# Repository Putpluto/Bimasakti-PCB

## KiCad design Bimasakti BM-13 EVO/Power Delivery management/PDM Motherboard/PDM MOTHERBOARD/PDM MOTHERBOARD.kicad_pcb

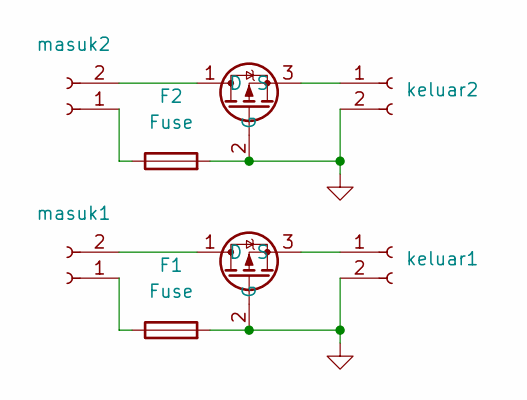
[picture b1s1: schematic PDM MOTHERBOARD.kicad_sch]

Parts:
F1, F2: Fuse; Fuseholder_Clip-5x20mm_Bel_FC-203-22_Lateral_P17.80x5.00mm_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
U1, U2: SOIC-8 (AOD)
keluar1, keluar2: JST_EH_B2B-EH-A_1x02_P2.50mm_Vertical
masuk1, masuk2: JST_EH_B2B-EH-A_1x02_P2.50mm_Vertical

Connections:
GND: F1.2, F2.2, U1.2 (G), U2.2 (G), keluar1.2, keluar2.2
unnamed: U1.1 (D), masuk1.2
unnamed: U1.3 (S), keluar1.1
unnamed: U2.1 (D), masuk2.2
unnamed: U2.3 (S), keluar2.1
unnamed: F1.1, masuk1.1
unnamed: F2.1, masuk2.1

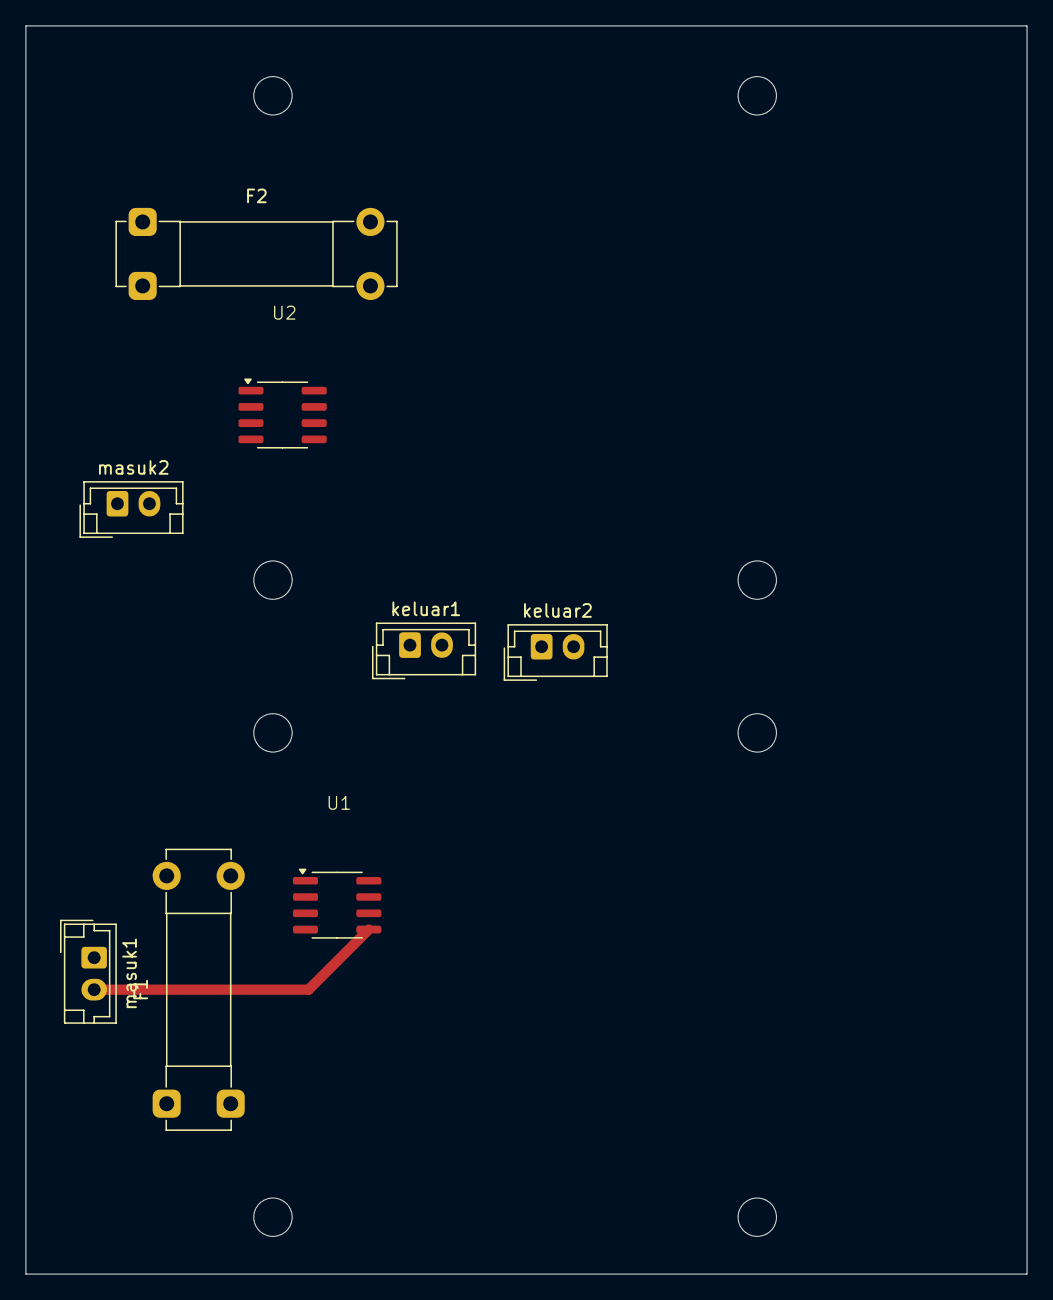
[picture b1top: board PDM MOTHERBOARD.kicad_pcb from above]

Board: 2 copper layers, 78.2 x 97.5 mm, 8 parts (0 on the bottom side), 7 nets.

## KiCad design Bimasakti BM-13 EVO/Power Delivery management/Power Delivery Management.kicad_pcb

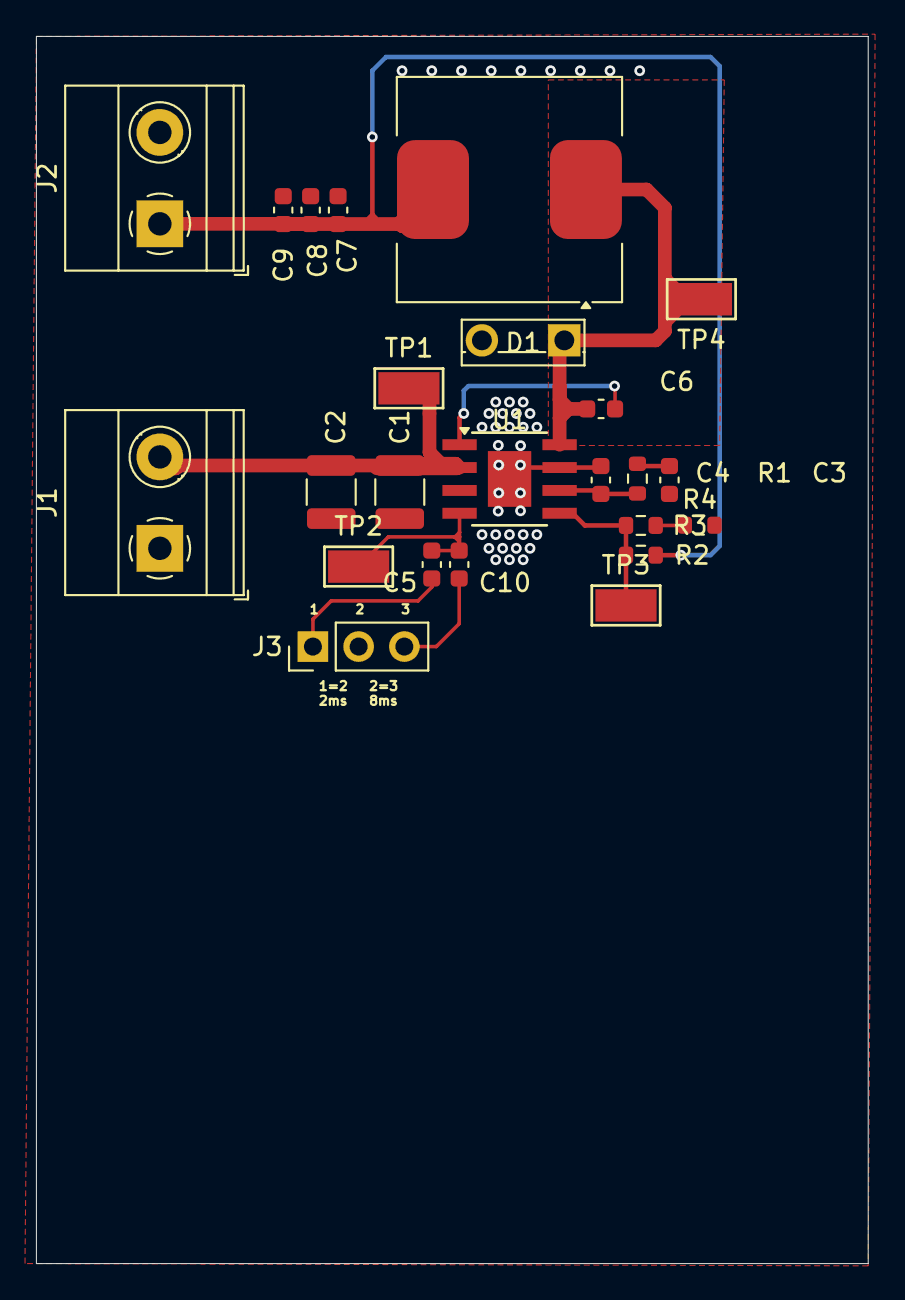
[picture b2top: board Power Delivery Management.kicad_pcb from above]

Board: 4 copper layers, 46.2 x 68.2 mm, 24 parts (0 on the bottom side), 12 nets.

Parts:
C1, C2: 22uF; C_1210_3225Metric
C3: 1nF; C_0603_1608Metric
C4: 10pF; C_0603_1608Metric
C5: 5nF; C_0603_1608Metric
C6: 100nF; C_0603_1608Metric
C7, C8, C9: 47uF; C_0603_1608Metric
C10: 20nF; C_0603_1608Metric
D1: 950mV 10A; TO-251-2_Vertical
J1: 12V Accu; TerminalBlock_Phoenix_MKDS-1,5-2-5.08_1x02_P5.08mm_Horizont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
J2: 5V Out; TerminalBlock_Phoenix_MKDS-1,5-2-5.08_1x02_P5.08mm_Horizont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
J3: Slow Start; PinHeader_1x03_P2.54mm_Vertical
L1: 12uH; L_Coilcraft_MSS1278T-XXX
R1: 50k; R_0603_1608Metric
R2: 10k; R_0603_1608Metric
R3: 1.5k; R_0603_1608Metric
R4: 390; R_0603_1608Metric
TP1, TP2, TP3, TP4: TestPoint; TestPoint_Keystone_5015_Micro-Minature
U1: TI_SO-PowerPAD-8

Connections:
+12V: C1.1, C2.1, J1.2, TP1.1, U1.2 (Vin)
/+5V: C7.1, C8.1, C9.1, J2.1, L1.2, R2.1
BOOT: C6.1, U1.1 (BOOT)
COMP: C4.1, R1.1, U1.6 (COMP)
GND: C1.2, C2.2, C3.2, C4.2, C7.2, C8.2, C9.2, D1.2 (A), J1.1, J2.2, J3.2, R4.2, U1.7 (GND), U1.9 (Power_PAD)
unnamed: C3.1, R1.2
unnamed: R3.1, R4.1
unnamed: C5.2, C10.2, TP2.1, U1.4 (SS)
PH: C6.2, D1.1 (K), L1.1, TP4.1, U1.8 (PH)
SS1: C5.1, J3.1
SS2: C10.1, J3.3
VSENSE: R2.2, R3.2, TP3.1, U1.5 (VSENSE)

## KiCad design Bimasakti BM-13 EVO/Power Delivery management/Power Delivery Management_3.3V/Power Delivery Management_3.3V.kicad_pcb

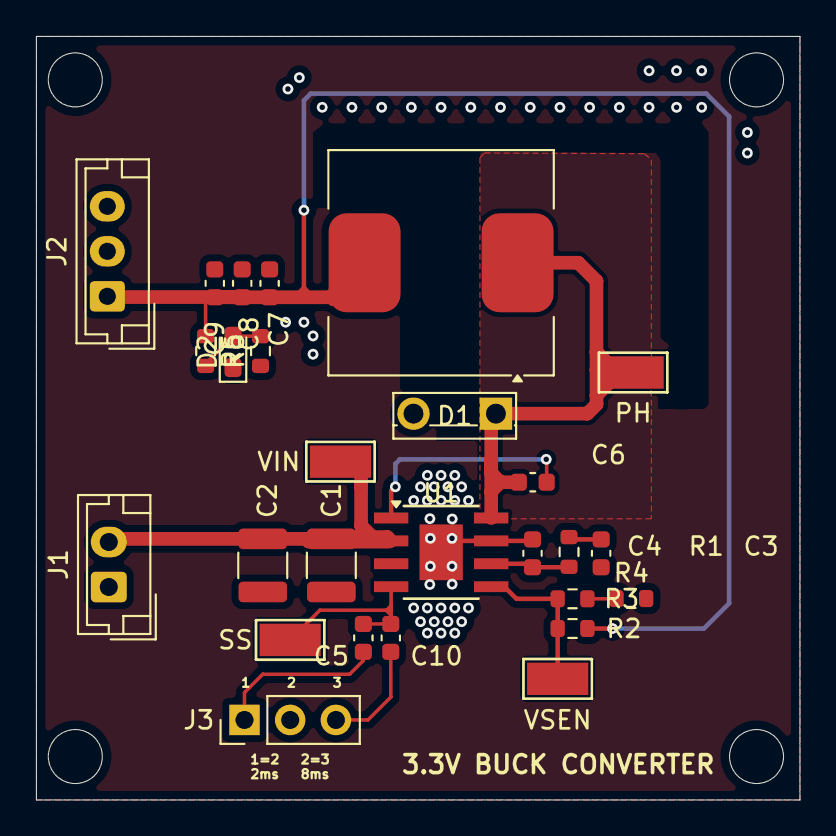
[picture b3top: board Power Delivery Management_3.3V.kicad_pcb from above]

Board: 2 copper layers, 42.4 x 42.4 mm, 27 parts (0 on the bottom side), 2 nets.

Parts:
C1, C2: 22uF; C_1210_3225Metric
C3: 1nF; C_0603_1608Metric
C4: 10pF; C_0603_1608Metric
C5: 5nF; C_0603_1608Metric
C6: 100nF; C_0603_1608Metric
C7, C8, C9: 47uF; C_0603_1608Metric
C10: 20nF; C_0603_1608Metric
D1: 950mV 10A; TO-251-2_Vertical
D2: LED; LED_0603_1608Metric_Pad1.05x0.95mm_HandSolder
J1: +12V In; JST_EH_B2B-EH-A_1x02_P2.50mm_Vertical
J2: Conn_01x03_Socket; JST_EH_B3B-EH-A_1x03_P2.50mm_Vertical
J3: Slow Start; PinHeader_1x03_P2.54mm_Vertical
L1: 12uH; L_Coilcraft_MSS1278T-XXX
PH: TestPoint; TestPoint_Keystone_5015_Micro-Minature
R1: 50k; R_0603_1608Metric
R2: 10k; R_0603_1608Metric
R3, R6: 1.5k; R_0603_1608Metric
R4: 390; R_0603_1608Metric
R5: 1k; R_0603_1608Metric
SS: TestPoint; TestPoint_Keystone_5015_Micro-Minature
U1: TI_SO-PowerPAD-8
VIN: TestPoint; TestPoint_Keystone_5015_Micro-Minature
VSEN: TestPoint; TestPoint_Keystone_5015_Micro-Minature

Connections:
GND: D2.1 (K), R6.1
unnamed: D2.2 (A), R5.2, R6.2

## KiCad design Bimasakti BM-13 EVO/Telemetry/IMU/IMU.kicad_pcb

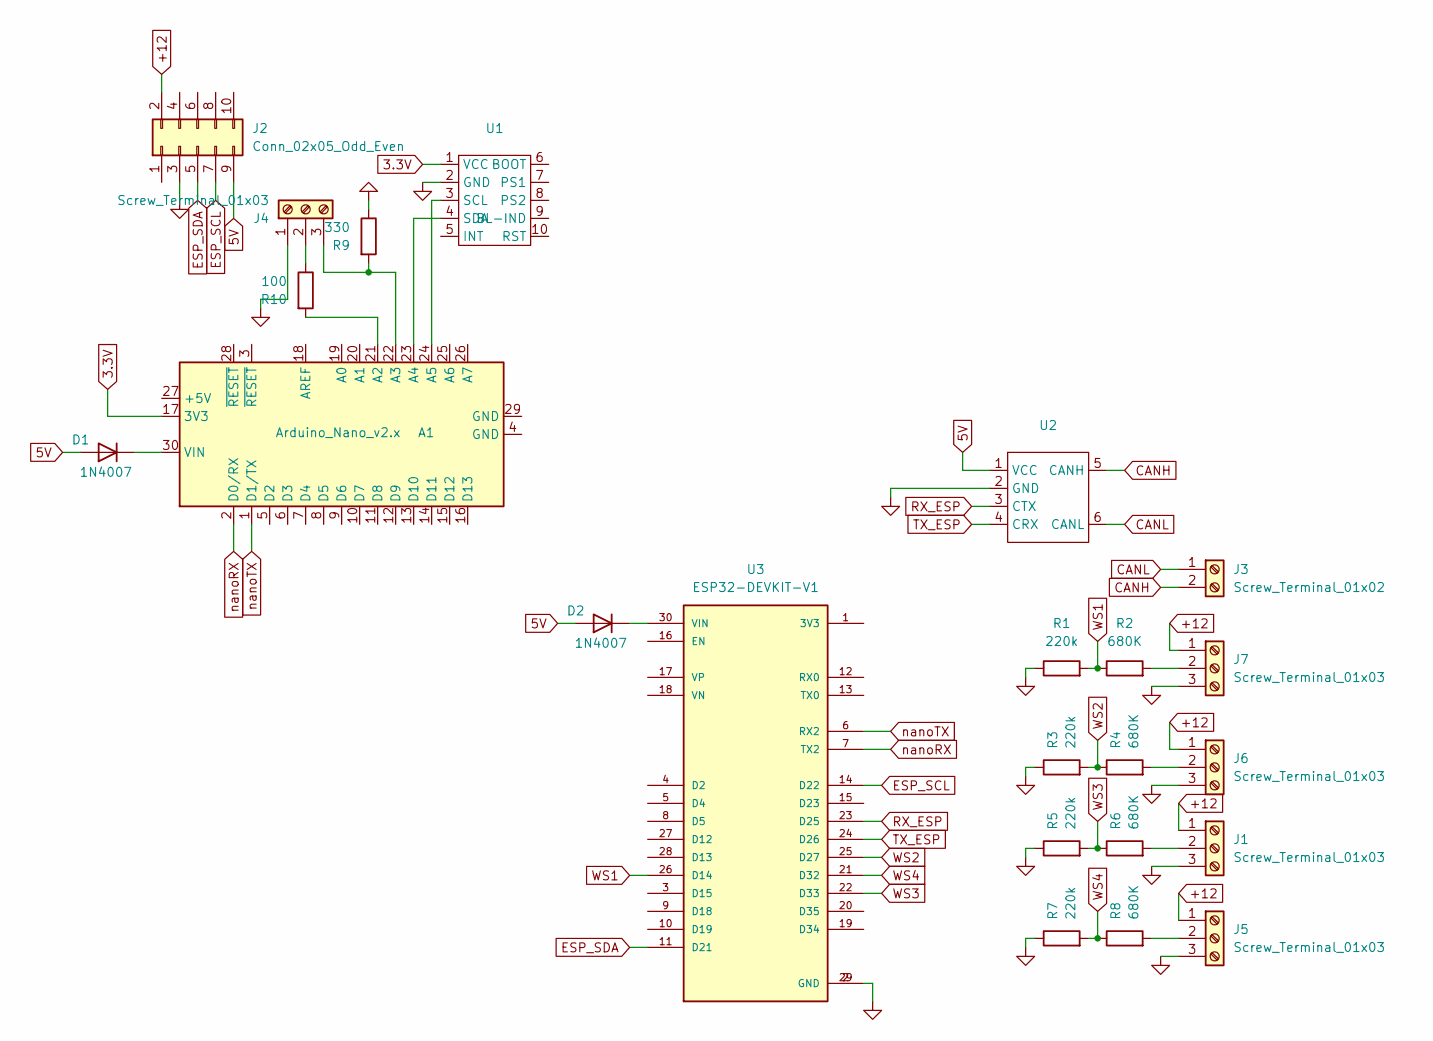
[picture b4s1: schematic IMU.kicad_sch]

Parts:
A1: Arduino_Nano_v2.x; Arduino_Nano
D1, D2: 1N4007; D_DO-41_SOD81_P7.62mm_Horizontal
J1, J5, J6, J7: Screw_Terminal_01x03; TerminalBlock_Phoenix_MKDS-3-3-5.08_1x03_P5.08mm_Horizontal
J2: Conn_02x05_Odd_Even; IDC-Header_2x05_P2.54mm_Vertical
J3: Screw_Terminal_01x02; TerminalBlock_Phoenix_MKDS-1,5-2-5.08_1x02_P5.08mm_Horizont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
J4: Screw_Terminal_01x03; TerminalBlock_Phoenix_MKDS-1,5-3-5.08_1x03_P5.08mm_Horizont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
R1, R3, R5, R7: 220k; R_Axial_DIN0207_L6.3mm_D2.5mm_P7.62mm_Horizontal
R2, R4, R6, R8: 680K; R_Axial_DIN0207_L6.3mm_D2.5mm_P7.62mm_Horizontal
R9: 330; R_Axial_DIN0207_L6.3mm_D2.5mm_P7.62mm_Horizontal
R10: 100; R_Axial_DIN0207_L6.3mm_D2.5mm_P7.62mm_Horizontal
U1: BNO055
U2: MCP2551
U3: ESP32-DEVKIT-V1; MODULE_ESP32_DEVKIT_V1; PARTREV N/A

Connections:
3.3V: A1.17 (3V3), U1.1 (VCC)
5V: D1.2 (A), D2.2 (A), J2.9, U2.1 (VCC)
+12: J1.1, J2.2, J5.1, J6.1, J7.1
CANH: J3.2, U2.5 (CANH)
CANL: J3.1, U2.6 (CANL)
ESP_SCL: J2.7, U3.14 (D22)
ESP_SDA: J2.5, U3.11 (D21)
GND: J1.3, J2.3, J4.1, J5.3, J6.3, J7.3, R1.1, R3.1, R5.1, R7.1, R9.1, U1.2 (GND), U2.2 (GND), U3.2 (GND), U3.29 (GND)
unnamed: A1.21 (A2), R10.2
unnamed: A1.22 (A3), J4.3, R9.2
unnamed: A1.23 (A4), U1.4 (SDA)
unnamed: A1.24 (A5), U1.3 (SCL)
unnamed: A1.30 (VIN), D1.1 (K)
unnamed: D2.1 (K), U3.30 (VIN)
unnamed: J1.2, R6.2
unnamed: J4.2, R10.1
unnamed: J5.2, R8.2
unnamed: J6.2, R4.2
unnamed: J7.2, R2.2
RX_ESP: U2.3 (CTX), U3.23 (D25)
TX_ESP: U2.4 (CRX), U3.24 (D26)
WS1: R1.2, R2.1, U3.26 (D14)
WS2: R3.2, R4.1, U3.25 (D27)
WS3: R5.2, R6.1, U3.22 (D33)
WS4: R7.2, R8.1, U3.21 (D32)
nanoRX: A1.2 (D0/RX), U3.7 (TX2)
nanoTX: A1.1 (D1/TX), U3.6 (RX2)

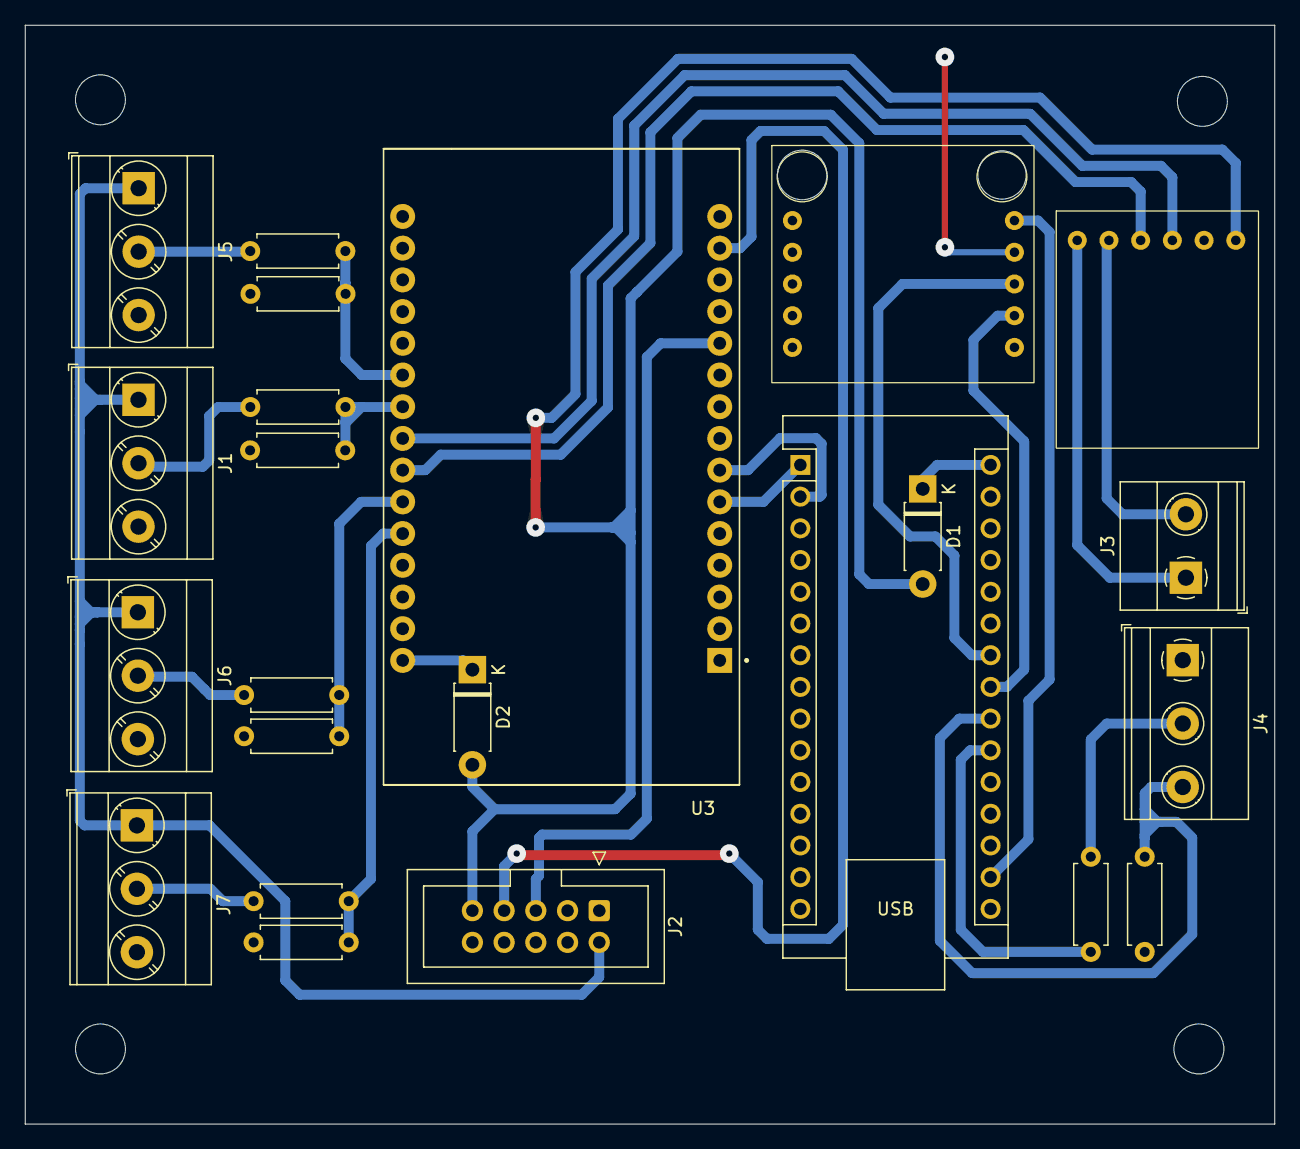
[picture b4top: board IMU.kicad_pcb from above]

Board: 2 copper layers, 100.1 x 88.0 mm, 23 parts (0 on the bottom side), 27 nets.

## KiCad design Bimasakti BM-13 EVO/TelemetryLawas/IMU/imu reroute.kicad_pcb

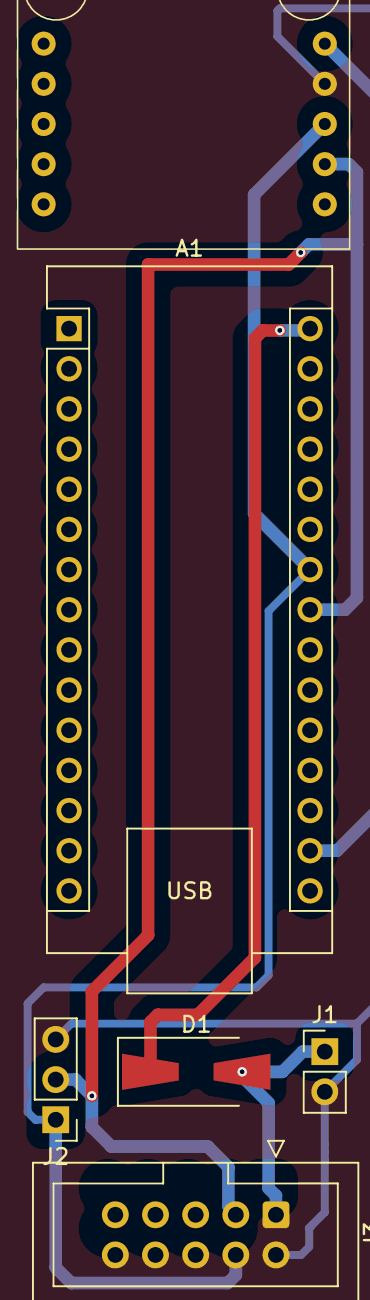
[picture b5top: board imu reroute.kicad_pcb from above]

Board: 2 copper layers, 6 parts (0 on the bottom side), 6 nets.

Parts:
A1: Arduino_Nano_v2.x; Arduino_Nano
D1: 1N4007; D_SMA-SMB_Universal_Handsoldering
J1: Conn_01x02_Pin; PinHeader_1x02_P2.54mm_Vertical
J2: Conn_01x03_Pin; PinHeader_1x03_P2.54mm_Vertical
J3: Conn_02x05_Counter_Clockwise; IDC-Header_2x05_P2.54mm_Vertical
U1: BNO055

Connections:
3.3V: A1.17 (3V3), U1.1 (VCC)
GND: J1.2, J2.3, J3.2, U1.2 (GND)
unnamed: A1.23 (A4), J2.2, J3.3, U1.4 (SDA)
unnamed: A1.24 (A5), J2.1, J3.4, U1.3 (SCL)
unnamed: A1.30 (VIN), D1.1 (K)
unnamed: D1.2 (A), J1.1, J3.1

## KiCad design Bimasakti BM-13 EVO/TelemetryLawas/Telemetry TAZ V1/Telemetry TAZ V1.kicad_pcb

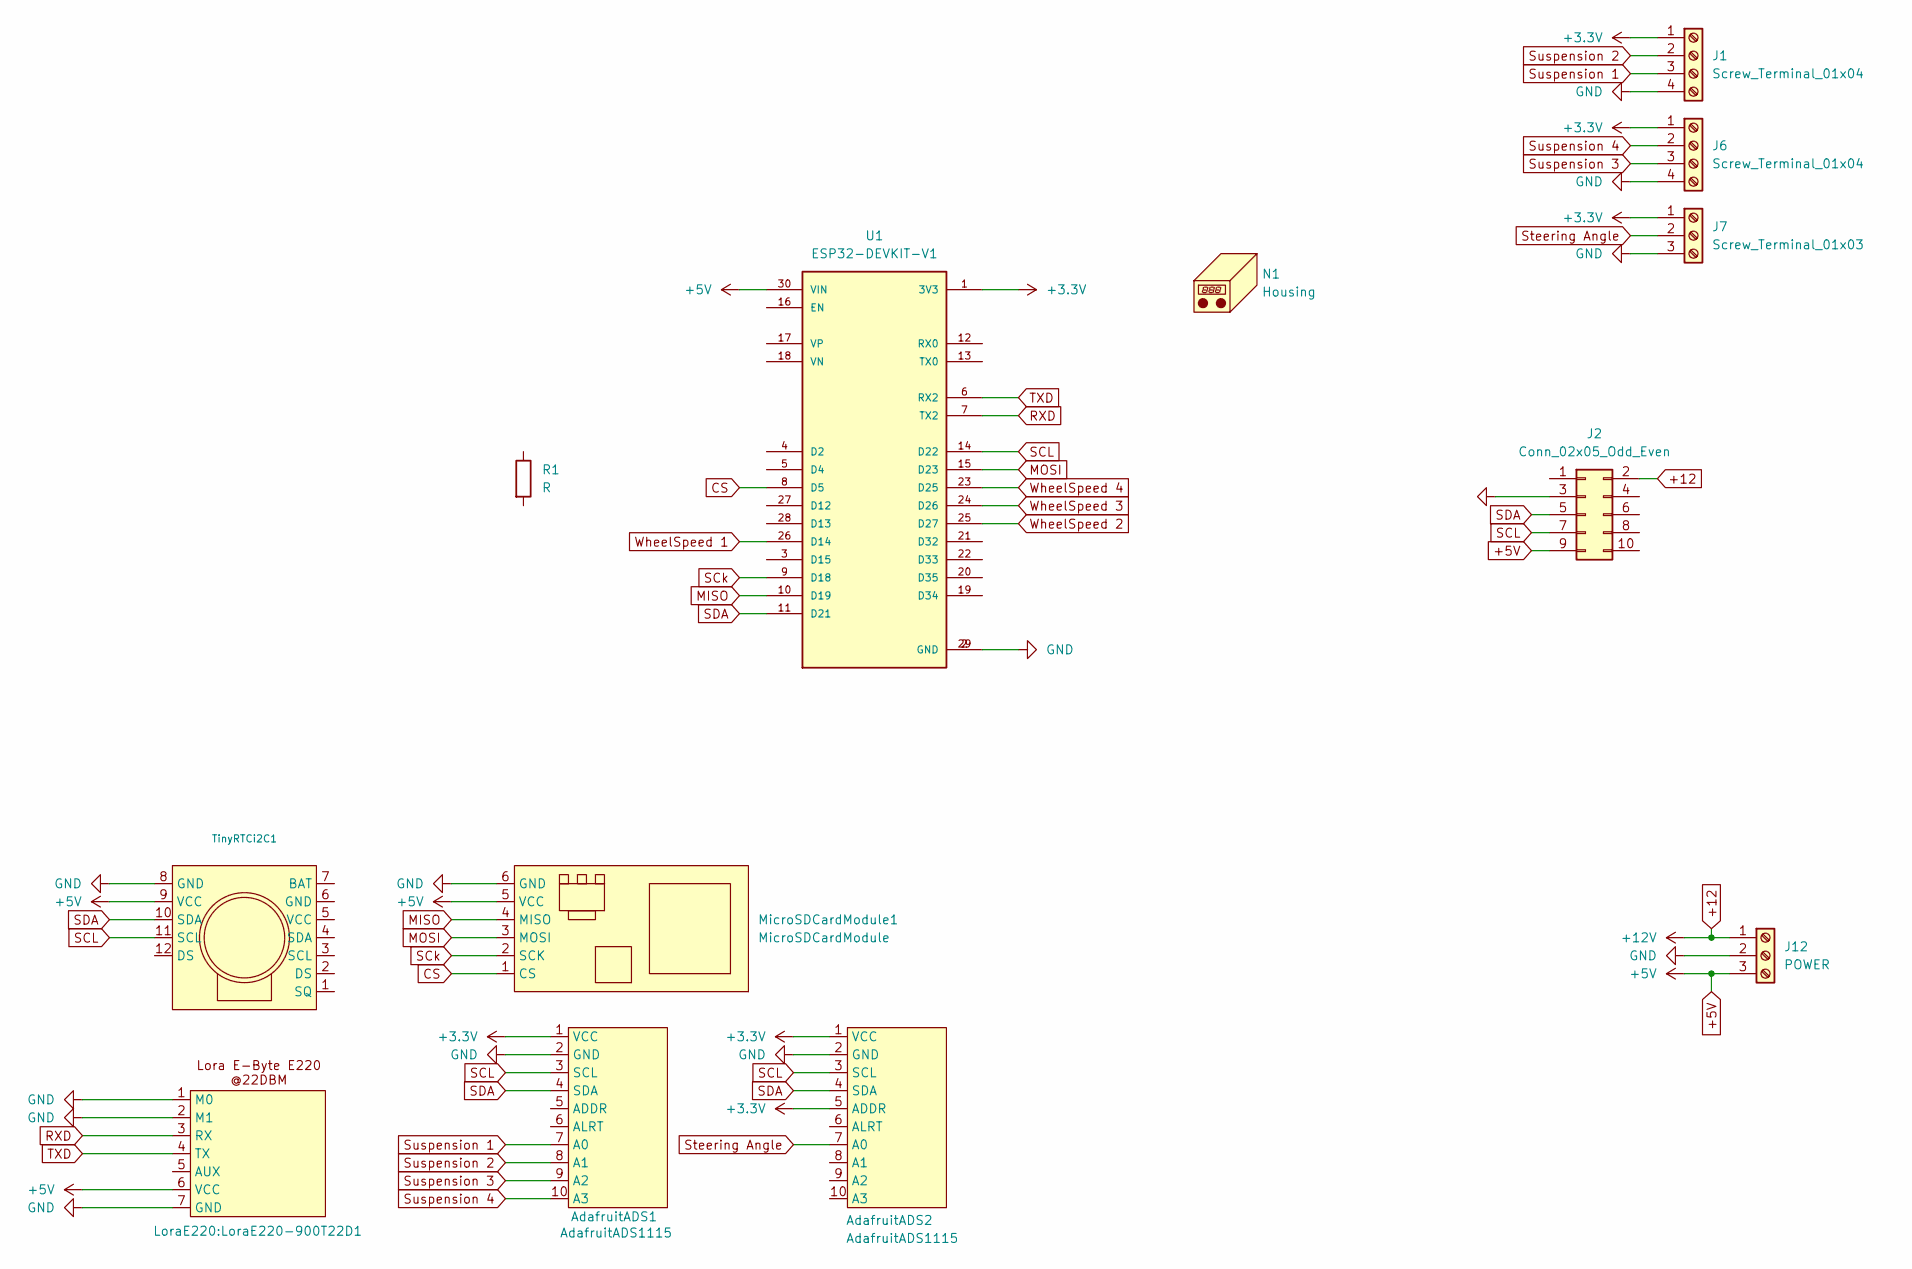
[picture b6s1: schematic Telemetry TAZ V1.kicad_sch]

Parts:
AdafruitADS1, AdafruitADS2: AdafruitADS1115; Adafruit ADS1115
J1, J6: Screw_Terminal_01x04; TerminalBlock_Phoenix_MKDS-1,5-4-5.08_1x04_P5.08mm_Horizont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
J2: Conn_02x05_Odd_Even; IDC-Header_2x05_P2.54mm_Vertical
J7: Screw_Terminal_01x03; TerminalBlock_Phoenix_MKDS-1,5-3-5.08_1x03_P5.08mm_Horizont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
J12: POWER; TerminalBlock_Phoenix_MKDS-1,5-3-5.08_1x03_P5.08mm_Horizont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
LoraE220:LoraE220-900T22D1: Lora E220-900T22D
MicroSDCardModule1: MicroSDCardModule; MicroSDCard Module Inverted
N1: Housing; IMU_Stackup
R1: R
TinyRTCi2C1: Tiny RTC i2C
U1: ESP32-DEVKIT-V1; MODULE_ESP32_DEVKIT_V1; PARTREV N/A

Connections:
+3.3V: AdafruitADS1.1 (VCC), AdafruitADS2.1 (VCC), AdafruitADS2.5 (ADDR), J1.1, J6.1, J7.1, U1.1 (3V3)
+5V: J2.9, J12.3, LoraE220:LoraE220-900T22D1.6 (VCC), MicroSDCardModule1.5 (VCC), TinyRTCi2C1.9 (VCC), U1.30 (VIN)
+12: J2.2, J12.1
CS: MicroSDCardModule1.1 (CS), U1.8 (D5)
GND: AdafruitADS1.2 (GND), AdafruitADS2.2 (GND), J1.4, J2.3, J6.4, J7.3, J12.2, LoraE220:LoraE220-900T22D1.1 (M0), LoraE220:LoraE220-900T22D1.2 (M1), LoraE220:LoraE220-900T22D1.7 (GND), MicroSDCardModule1.6 (GND), TinyRTCi2C1.8 (GND), U1.2 (GND), U1.29 (GND)
MISO: MicroSDCardModule1.4 (MISO), U1.10 (D19)
MOSI: MicroSDCardModule1.3 (MOSI), U1.15 (D23)
RXD: LoraE220:LoraE220-900T22D1.3 (RX), U1.7 (TX2)
SCL: AdafruitADS1.3 (SCL), AdafruitADS2.3 (SCL), J2.7, TinyRTCi2C1.11 (SCL), U1.14 (D22)
SCk: MicroSDCardModule1.2 (SCK), U1.9 (D18)
SDA: AdafruitADS1.4 (SDA), AdafruitADS2.4 (SDA), J2.5, TinyRTCi2C1.10 (SDA), U1.11 (D21)
Steering Angle: AdafruitADS2.7 (A0), J7.2
Suspension 1: AdafruitADS1.7 (A0), J1.3
Suspension 2: AdafruitADS1.8 (A1), J1.2
Suspension 3: AdafruitADS1.9 (A2), J6.3
Suspension 4: AdafruitADS1.10 (A3), J6.2
TXD: LoraE220:LoraE220-900T22D1.4 (TX), U1.6 (RX2)
WheelSpeed 1: U1.26 (D14)
WheelSpeed 2: U1.25 (D27)
WheelSpeed 3: U1.24 (D26)
WheelSpeed 4: U1.23 (D25)

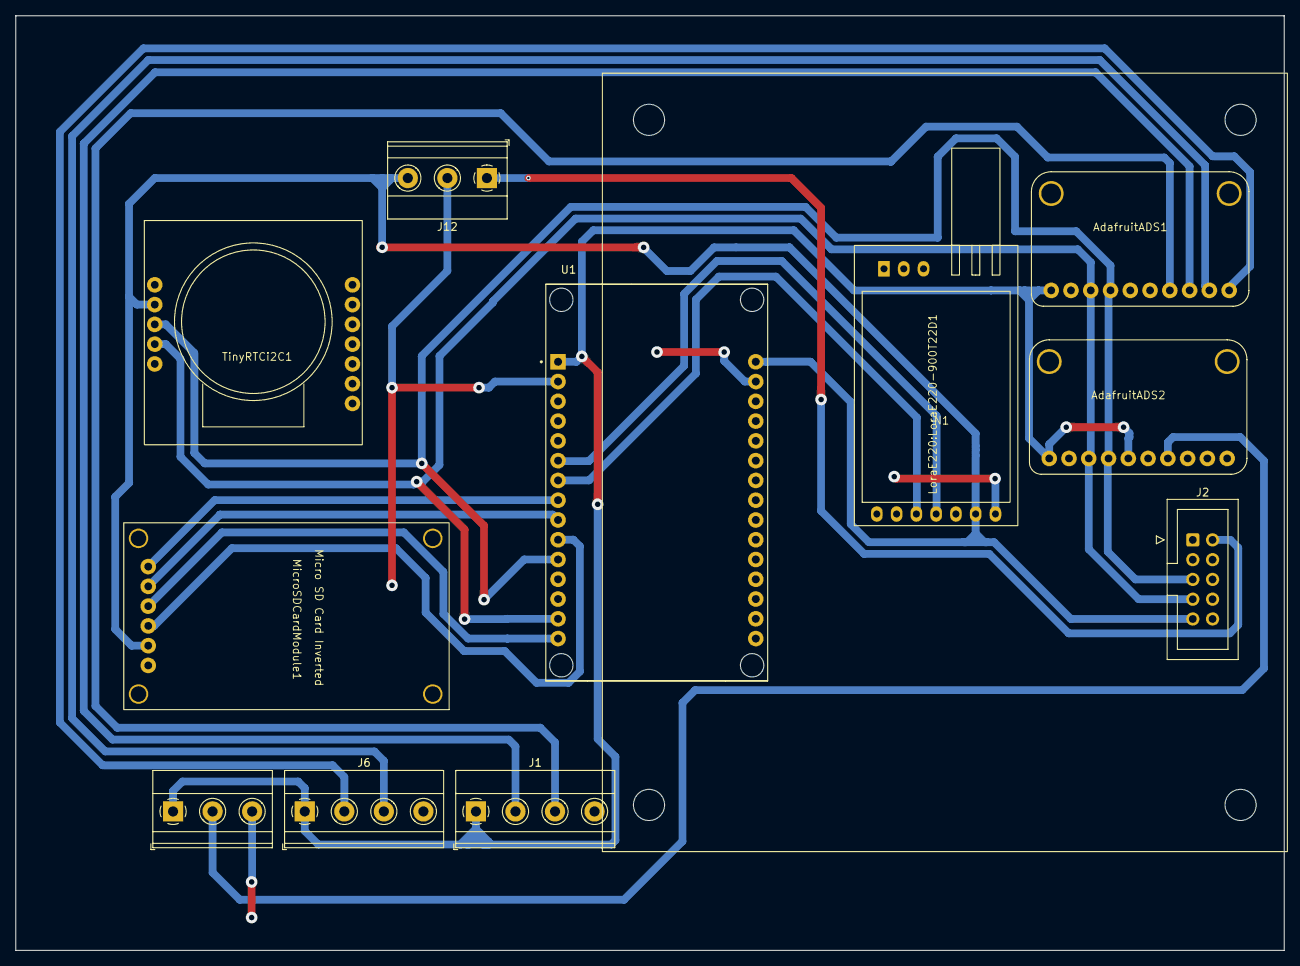
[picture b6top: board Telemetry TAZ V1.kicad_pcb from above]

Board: 2 copper layers, 163.0 x 120.1 mm, 12 parts (0 on the bottom side), 17 nets.

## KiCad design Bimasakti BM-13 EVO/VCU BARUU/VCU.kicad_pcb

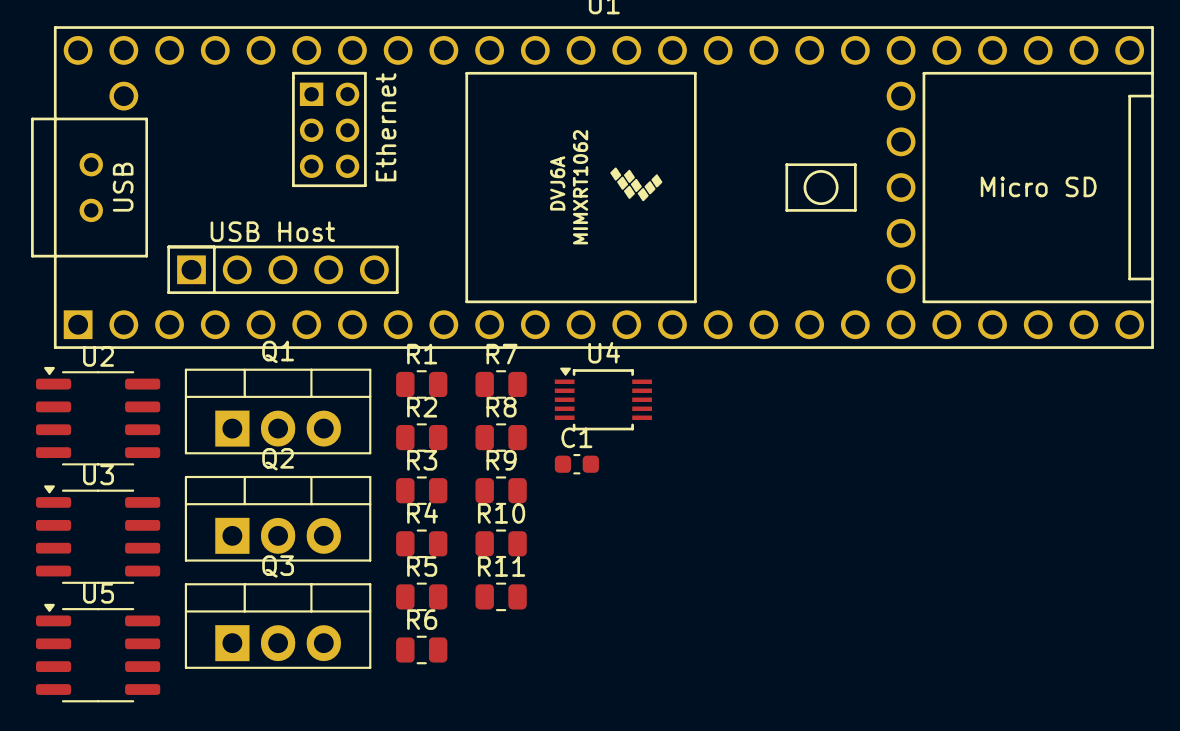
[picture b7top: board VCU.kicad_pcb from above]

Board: 2 copper layers, 20 parts (0 on the bottom side), 17 nets, no tracks yet.

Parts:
C1: 0.1uF; C_0603_1608Metric
Q1, Q2, Q3: IRLZ44N; TO-220-3_Vertical
R1, R2, R3, R4, R7, R8: R; R_0805_2012Metric
R5, R6: 10K; R_0805_2012Metric
R9, R10, R11: 1K; R_0805_2012Metric
U1: Teensy4.1; Teensy41
U2, U3, U5: SN65HVD230; SOIC-8_3.9x4.9mm_P1.27mm
U4: ADS1115IDGS; TSSOP-10_3x3mm_P0.5mm

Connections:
3V3: C1.2, R5.1, R6.1, U2.3 (VCC), U3.3 (VCC), U4.8 (VDD), U5.3 (VCC)
ANA_GND: C1.1, U2.2 (GND), U3.2 (GND), U4.1 (ADDR), U4.3 (GND), U5.2 (GND)
CANH1: R1.1, U2.7 (CANH)
CANH2: R2.1, U3.7 (CANH)
CANH3: R8.1, U5.7 (CANH)
CANL1: R1.2, U2.6 (CANL)
CANL2: R2.2, U3.6 (CANL)
CANL3: R8.2, U5.6 (CANL)
D1: Q1.1 (G), R11.1
D2: Q2.1 (G), R10.1
D3: Q3.1 (G), R9.1
GND: Q1.3 (S), Q2.3 (S), Q3.3 (S), R3.1, R4.1, R7.1, R9.2, R10.2, R11.2, U1.47 (GND)
unnamed: R3.2, U2.8 (Rs)
unnamed: R4.2, U3.8 (Rs)
unnamed: R7.2, U5.8 (Rs)
SCL: R5.2, U4.10 (SCL)
SDA: R6.2, U4.9 (SDA)
